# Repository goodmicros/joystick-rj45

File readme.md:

# Joystick

A retro style joystick with arcade parts and an rj45 port for easy cable management.

## assembly

Joystick fits only in non-standard orientation. no metal plate needed.  

## files

* [3d files](https://cad.onshape.com/documents/96a650fb4ce966bf403bef14/w/71dfbdc1e70c6a02d147e938/e/68f93b33a388599ce0cc54c4?renderMode=0&uiState=69bbfd8464b455470806eaa5)
    * [top.stl](3d/joystick-top.stl)
    * [bottom.stl](3d/joystick-bot.stl)
* joystick pcb
    * [gerber](joystick-pcb/output/joystick-gerber.zip)
    * [.step](joystick-pcb/joystic-pcb.step)
* commodore adapter pcb
    * [gerber](commodore-adapter/output/commodore-adapter-gerber.zip)
    * [.step](commodore-adapter/output/commodore-adapter.step)

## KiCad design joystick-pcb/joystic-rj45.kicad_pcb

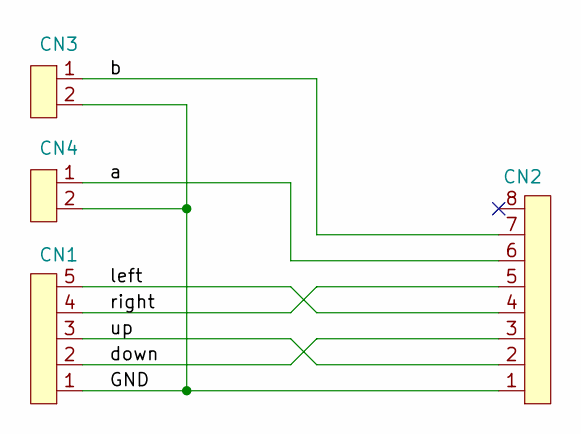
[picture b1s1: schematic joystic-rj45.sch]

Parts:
CN1: 1x5; xh-5
CN2: 1x8; RJHSE-5080
CN3, CN4: 1x2; xh-2

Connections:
/GND: CN1.1, CN2.1, CN3.2, CN4.2
/a: CN2.6, CN4.1
/b: CN2.7, CN3.1
/down: CN1.2, CN2.3
/left: CN1.5, CN2.4
/right: CN1.4, CN2.5
/up: CN1.3, CN2.2

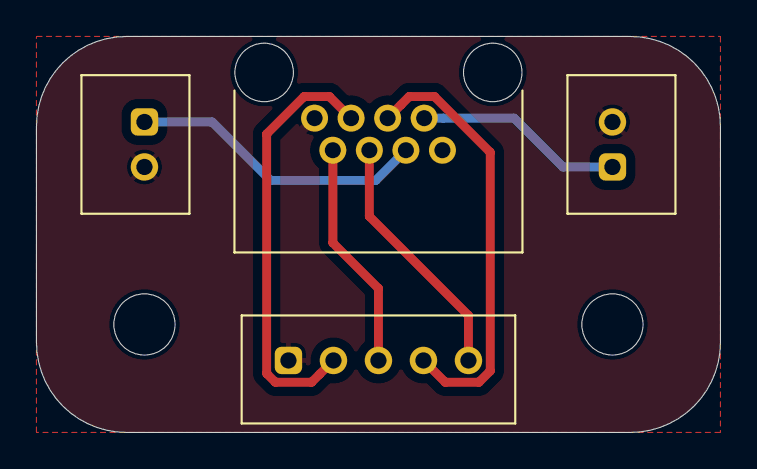
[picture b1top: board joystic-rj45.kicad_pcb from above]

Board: 2 copper layers, 38.0 x 22.0 mm, 4 parts (0 on the bottom side), 7 nets.

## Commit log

2026-03-19 moved pcb files to own directory. added link to 3d files
2026-03-19 added .stl files for case
2026-04-16 added info on joystick orientation
2026-04-16 added commodore adapter pcb to this project. created gerbers
2026-04-16 thickened bottom plate. added 5mm height on the inside
2026-04-20 fixed DB9 pinout from male to female
2026-05-04 added 3d models for commodore adapter and it's case
